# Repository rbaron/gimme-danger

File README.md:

An open source [USB Power Delivery](https://en.wikipedia.org/wiki/USB_hardware#USB_Power_Delivery) trigger board and 5-channel PWM controller that runs [ESPHome](https://esphome.io).

_GIMME DANGER!!_ negotiates up to 21 V and 3 A[^1] from a USB Power Delivery (USB-PD) capable source -- such as common USB-C wall adapters/chargers and power banks -- and provides controls for its 5 PWM channels, optionally via [Home Assistant](https://home-assistant.io). Each channel can be used to interface with LEDs, motors and more. See below for some video demos.

# Hardware

* [ESP32-S3](https://www.espressif.com/en/products/socs/esp32-s3) module, mounted on the [back of the PCB](./media/gimme-danger-back.jpg)
* [FUSB302B](https://www.onsemi.com/products/interfaces/usb-type-c/fusb302b) USB-PD controller
* [INA219](https://www.ti.com/product/INA219) current sensor
* 5 output PWM channels
* 2x5.5mm barrel jack for raw output voltage access
* Optional OLED display

The [`kicad/`](./kicad/) directory contains design files and fabrication files for [JLCPCB](https://jlcpcb.com) manufacturing and assembly. The big through-hole components (headers, power terminals) and the ESP32-S3 module are not included in the assembly, and expected to be soldered by hand.

# Software
A custom `fusb302` component was implemented in ESPHome to support this project. It currently lives in its own fork on [github.com/rbaron/tree/fusb302](https://github.com/rbaron/esphome/tree/fusb302).

Here's a minimal example of using our custom `fusb302` component with ESPHome:

```yaml
external_components:
  - source:
      type: git
      url: https://github.com/rbaron/esphome
      ref: fusb302
    components: [fusb302]

fusb302:
  id: fusb302_id
  i2c_id: i2c_bus_fusb302
  interrupt_pin: GPIO5
  voltage: 12000 mV
  current: 1000 mA
  on_pd_negotiation_success:
    then:
      - switch.turn_on: load_switch
```

Full ESPHome configs for the demos below and more are available in the [`code/`](./code) directory.

# ‼️ Safety disclaimer ‼️
Configuration mistakes or software bugs may toast your devices if a high voltage is accidentally negotiated. While I have never run into these issues, even during development, be extra mindful of this fact then using this project or the `fusb302` component separately. For all intents and purposes, this is an experimental project. Use it at your own risk.

# Supported Power Delivery features
* USB-PD 2.0 Fixed voltages -- 5V, 9V, 12V, 15V, 20V
* USB-PD 3.0 Programmable Power Supply (PPS) -- 3.3V-21V, in 20mV steps (see the power supply demo below)
* USB-PD 3.1 Extended Power Range (EPR) Fixed PDOs -- 28V[^1]

Support for USB-PD 3.1 Adjustable Voltage Supply (AVS) in EPR mode will let us pull 15-28V[^1]. Unfortunately it's still difficult to get our hands on EPR AVS capable sources to implement and test support for it, but in theory the heavy lifting is already done.

# Some use cases & demos
Below there are some demo videos. Click on the images to play.

## 12V LED strip
The main motivation for this project was to power short runs of LED strips from USB-C chargers and control them via Home Assistant. Observing the maximum current and voltage[^1], it should be doable to light up a shelf, table, TV stand or any DYI project that requires only a couple of meters of 12V LED strips. Here [wled-calculator.github.io](https://wled-calculator.github.io/) should help with planning.

In the video below we see _GIMME DANGER!!_ connected to [Home Assistant](https://www.home-assistant.io), controlling a short 12V LED strip.

## 12V RGBW LED strip

## A lil' programmable power supply
What's fun is that we can negotiate voltages on the fly from USB-PD 3.0 sources that offer Programmable Power Supply (PPS) modes. Here we have a potentiometer that sets the target voltage, and a button that triggers the USB-PD negotiation for that voltage.

A tiny, experimental and largely untested power supply that's powered by the same USB-C charger as my [soldering iron](https://pine64.com/product/pinecil-smart-mini-portable-soldering-iron/)? Straight into my toolbox.

## A Home Assistant controlled power supply
As a display of the flexibility of ESPHome and Home Assistant, we can use _GIMME DANGER!!_ to make a WiFi-controlled power supply. This is an objectively terrible idea, but it's not _GIMME SAFETY!!_ after all. Disregarding the risk of accidentally toasting our loads either via a misclick or a bug, this may be useful for automating the collection of I-V curves.

# Optional OLED display
There are female pin headers on the board to connect an 0.91" OLED display like [this one from Aliexpress](https://aliexpress.com/item/1005004816561244.html). It's used to display the running voltage and current. There's also a cute animation when negotiation is succesful -- you can see it in the demos above.

# 3D printed case

The [`case/`](./case) directory contains a little 3D printable case. The PCB is optionally held in place by three M2 screws and threaded inserts.

# License
The hardware and associated design files are released under the [Creative Commons CC BY-SA 4.0](https://creativecommons.org/licenses/by-sa/4.0/) license. The code is released under the [MIT license](https://opensource.org/licenses/MIT).

# Attributions
The logo uses the [Faster One](https://fonts.google.com/specimen/Faster+One/about) font, released under the [Open Font License](https://openfontlicense.org/).

[^1]: FUSB302B's typical maximum voltage is 21 V, with 28 V as the absolute maximum. Each PWM channel is rated for 3 A. In theory the board supports up to 5 A, but a safer, better tested range is 21 V / 3 A in total.

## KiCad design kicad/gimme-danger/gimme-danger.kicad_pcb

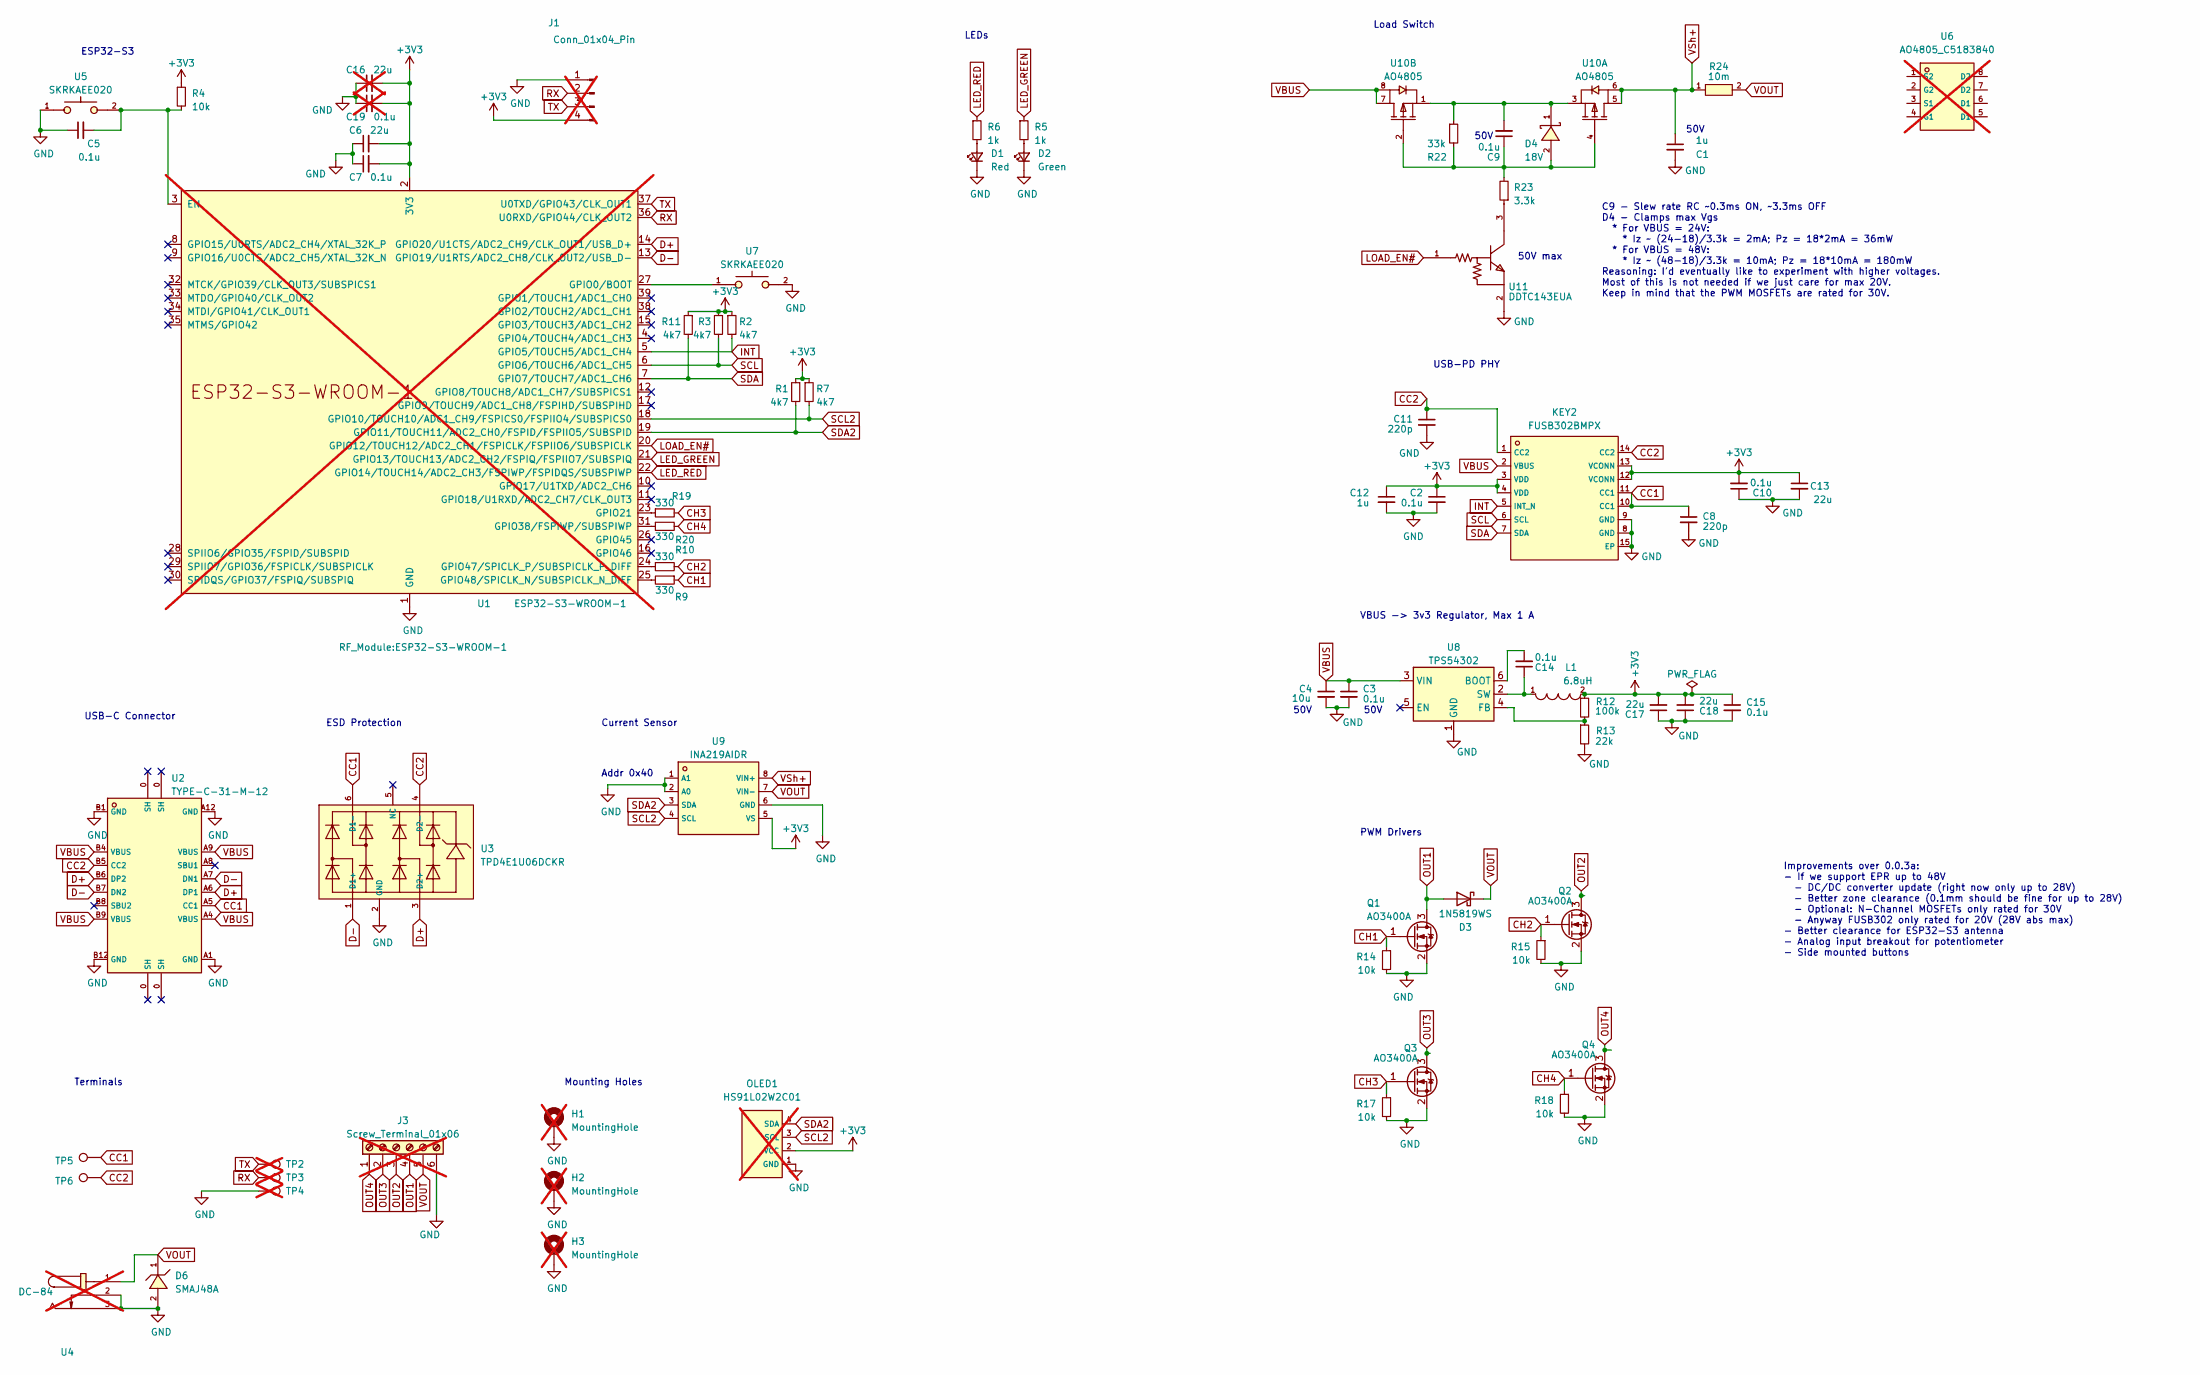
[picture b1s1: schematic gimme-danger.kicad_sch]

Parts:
C1: 1u; C_0603_1608Metric; LCSC C15849
C2, C3, C9, C10, C14, C15: 0.1u; C_0402_1005Metric; LCSC C307331
C4: 10u; C_0805_2012Metric; LCSC C440198
C5, C7: 0.1u; C_0402_1005Metric; LCSC C1525
C6, C13, C17, C18: 22u; C_0805_2012Metric; LCSC C45783
C8, C11: 220p; C_0402_1005Metric; LCSC C1530
C12: 1u; C_0402_1005Metric; LCSC C52923
C16: 22u; C_0805_2012Metric_Pad1.18x1.45mm_HandSolder; LCSC C45783; not fitted
C19: 0.1u; C_0805_2012Metric_Pad1.18x1.45mm_HandSolder; LCSC C1525; not fitted
D1: Red; LED_0805_2012Metric; LCSC C84256
D2: Green; LED_0805_2012Metric; LCSC C2297
D3: 1N5819WS; D_SOD-323
D4: 18V; SOD-523_L1.2-W0.8-LS1.6-RD; LCSC C327501
D6: SMAJ48A; SMA_L4.3-W2.5-LS5.0-RD; LCSC C353444
H1, H2, H3: MountingHole; MountingHole_2.2mm_M2_Pad_Via; not fitted
J1: Conn_01x04_Pin; PinHeader_1x04_P2.54mm_Vertical; not fitted
J3: Screw_Terminal_01x06; TerminalBlock_Phoenix_MKDS-1,5-6_1x06_P5.00mm_Horizontal; not fitted
KEY2: FUSB302BMPX; MLP-14_L2.5-W2.5-P0.50-BL-EP; LCSC C132291
L1: 6.8uH; IND-SMD_L4.5-W4.5_SMMS0420; LCSC C133194
OLED1: HS91L02W2C01; OLED-TH_L38.0-W12.0_HS91L02W2C01; LCSC C5248081; not fitted
Q1, Q2, Q3, Q4: AO3400A; SOT-23; LCSC C347475
R1, R2, R3, R7, R11: 4k7; R_0402_1005Metric; LCSC C25900
R4, R14, R15, R17, R18: 10k; R_0402_1005Metric; LCSC C25744
R5, R6: 1k; R_0402_1005Metric; LCSC C11702
R9, R10, R19, R20: 330; R_0402_1005Metric; LCSC C25104
R12: 100k; R_0402_1005Metric; LCSC C25741
R13: 22k; R_0402_1005Metric; LCSC C25768
R22: 33k; R_0402_1005Metric; LCSC C25779
R23: 3.3k; R_0402_1005Metric; LCSC C25890
R24: 10m; R2512; LCSC C105366
TP2, TP3, TP4: 3v3; TestPoint_Pad_D1.0mm; not fitted
TP5, TP6: 3v3; TestPoint_Pad_D1.0mm
U1: ESP32-S3-WROOM-1; not fitted
U2: TYPE-C-31-M-12; USB-C_SMD-TYPE-C-31-M-12; LCSC C165948
U3: TPD4E1U06DCKR; SC-70-6_L2.2-W1.3-P0.65-LS2.1-BL; LCSC C194628
U4: DC-84; DC-IN-TH_DC-84; LCSC C718040; not fitted
U5, U7: SKRKAEE020; SW-SMD_L3.9-W3.0-P4.45; LCSC C115357
U6: AO4805_C5183840; SOP-8_L4.9-W3.9-P1.27-LS6.0-BL; LCSC C5183840; not fitted
U8: TPS54302; SOT-23-6; LCSC C311983
U9: INA219AIDR; SOIC-8_L4.9-W3.9-P1.27-LS6.0-BL; LCSC C138706
U10: AO4805; SOIC-8_L4.9-W3.9-P1.27-LS6.0-BL; LCSC C5183840
U11: DDTC143EUA; SOT-323-3_L2.0-W1.3-P1.30-LS2.1-BR; LCSC C460045

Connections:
+3V3: C2.1, C6.2, C7.2, C10.2, C12.1, C13.1, C15.1, C16.2, C17.2, C18.2, C19.2, J1.4, KEY2.3 (VDD), KEY2.4 (VDD), KEY2.12 (VCONN), KEY2.13 (VCONN), L1.2, OLED1.2 (VCC), R1.1, R2.1, R3.1, R4.1, R7.1, R11.1, R12.1, U1.2 (3V3), U9.5 (VS)
CC1: C8.1, KEY2.10 (CC1), KEY2.11 (CC1), TP5.1, U2.A5 (CC1), U3.6 (D1-)
CC2: C11.1, KEY2.1 (CC2), KEY2.14 (CC2), TP6.1, U2.B5 (CC2), U3.4 (D2-)
CH1: Q1.1 (G), R9.1, R14.1
CH2: Q2.1 (G), R10.2, R15.1
CH3: Q3.1 (G), R17.1, R19.2
CH4: Q4.1 (G), R18.1, R20.2
D+: U1.14 (GPIO20/U1CTS/ADC2_CH9/CLK_OUT1/USB_D+), U2.A6 (DP1), U2.B6 (DP2), U3.3 (D2+)
D-: U1.13 (GPIO19/U1RTS/ADC2_CH8/CLK_OUT2/USB_D-), U2.A7 (DN1), U2.B7 (DN2), U3.1 (D1+)
GND: C1.2, C2.2, C3.2, C4.2, C5.1, C6.1, C7.1, C8.2, C10.1, C11.2, C12.2, C13.2, C15.2, C16.1, C17.1, C18.1, C19.1, D1.1 (K), D2.1 (K), D6.2 (A), H1.1, H2.1, H3.1, J1.1, J3.6, KEY2.8 (GND), KEY2.9 (GND), KEY2.15 (EP), OLED1.1 (GND), Q1.2 (S), Q2.2 (S), Q3.2 (S), Q4.2 (S), R13.2, R14.2, R15.2, R17.2, R18.2, TP4.1, U1.1 (GND), U1.40 (GND), U1.41 (GND), U2.A1 (GND), U2.A12 (GND), U2.B1 (GND), U2.B12 (GND), U3.2 (GND), U4.2, U4.3, U5.1, U7.2, U8.1 (GND), U9.1 (A1), U9.2 (A0), U9.6 (GND), U11.2 (GND(0))
INT: KEY2.5 (INT_N), R2.2, U1.5 (GPIO5/TOUCH5/ADC1_CH4)
LED_GREEN: R5.1, U1.21 (GPIO13/TOUCH13/ADC2_CH2/FSPIQ/FSPIIO7/S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)
LED_RED: R6.1, U1.22 (GPIO14/TOUCH14/ADC2_CH3/FSPIWP/FSPIDQS/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)
LOAD_EN#: U1.20 (GPIO12/TOUCH12/ADC2_CH1/FSPICLK/FSPIIO6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), U11.1 (IN)
unnamed: D1.2 (A), R6.2
unnamed: D2.2 (A), R5.2
unnamed: C9.1, D4.2 (A), R22.2, R23.2, U10.2 (G2), U10.4 (G1)
unnamed: C9.2, D4.1 (K), R22.1, U10.1 (S2), U10.3 (S1)
unnamed: C5.2, R4.2, U1.3 (EN), U5.2
unnamed: U1.27 (GPIO0/BOOT), U7.1
unnamed: R19.1, U1.23 (GPIO21)
unnamed: R20.1, U1.31 (GPIO38/FSPIWP/SUBSPIWP)
unnamed: R10.1, U1.24 (GPIO47/SPICLK_P/SUBSPICLK_P_DIFF)
unnamed: R9.2, U1.25 (GPIO48/SPICLK_N/SUBSPICLK_N_DIFF)
unnamed: C14.2, U8.6 (BOOT)
unnamed: R12.2, R13.1, U8.4 (FB)
unnamed: C14.1, L1.1, U8.2 (SW)
unnamed: R23.1, U11.3 (OUT)
OUT1: D3.2 (A), J3.4, Q1.3 (D)
OUT2: J3.3, Q2.3 (D)
OUT3: J3.2, Q3.3 (D)
OUT4: J3.1, Q4.3 (D)
RX: J1.2, TP3.1, U1.36 (U0RXD/GPIO44/CLK_OUT2)
SCL: KEY2.6 (SCL), R3.2, U1.6 (GPIO6/TOUCH6/ADC1_CH5)
SCL2: OLED1.3 (SCL), R7.2, U1.18 (GPIO10/TOUCH10/ADC1_CH9/FSPICS0/FSPIIO4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), U9.4 (SCL)
SDA: KEY2.7 (SDA), R11.2, U1.7 (GPIO7/TOUCH7/ADC1_CH6)
SDA2: OLED1.4 (SDA), R1.2, U1.19 (GPIO11/TOUCH11/ADC2_CH0/FSPID/FSPIIO5/S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), U9.3 (SDA)
TX: J1.3, TP2.1, U1.37 (U0TXD/GPIO43/CLK_OUT1)
VBUS: C3.1, C4.1, KEY2.2 (VBUS), U2.A4 (VBUS), U2.A9 (VBUS), U2.B4 (VBUS), U2.B9 (VBUS), U8.3 (VIN), U10.7 (D2), U10.8 (D2)
VOUT: D3.1 (K), D6.1 (C), J3.5, R24.2, U4.1, U9.7 (VIN-)
VSh+: C1.1, R24.1, U9.8 (VIN+), U10.5 (D1), U10.6 (D1)

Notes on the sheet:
ESD Protection
Mounting Holes
Terminals
50V
Current Sensor
50V max
Improvements over 0.0.3a: - If we support EPR up to 48V - DC/DC converter update (right now only up to 28V) - Better zone clearance (0.1mm should be fine for up to 28V) - Optional: N-Channel MOSFETs only rated for 30V - Anyway FUSB302 only rated for 20V (28V abs max) - Better clearance for ESP32-S3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
USB-C Connector
VBUS -> 3v3 Regulator, Max 1 A
PWM Drivers
LEDs
Load Switch
ESP32-S3
C9 - Slew rate RC ~0.3ms ON, ~3.3ms OFF D4 - Clamps max Vgs * For VBUS = 24V: * Iz ~ (24-18)/3.3k = 2mA; Pz = 18*2mA = 36mW * For VBUS = 48V: * Iz ~ (48-18)/3.3k = 10mA; Pz = 18*10mA = 180mW Reasoning: I'd eventually like to experiment with higher voltages. Most of this is not needed if we just car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
USB-PD PHY
Addr 0x40

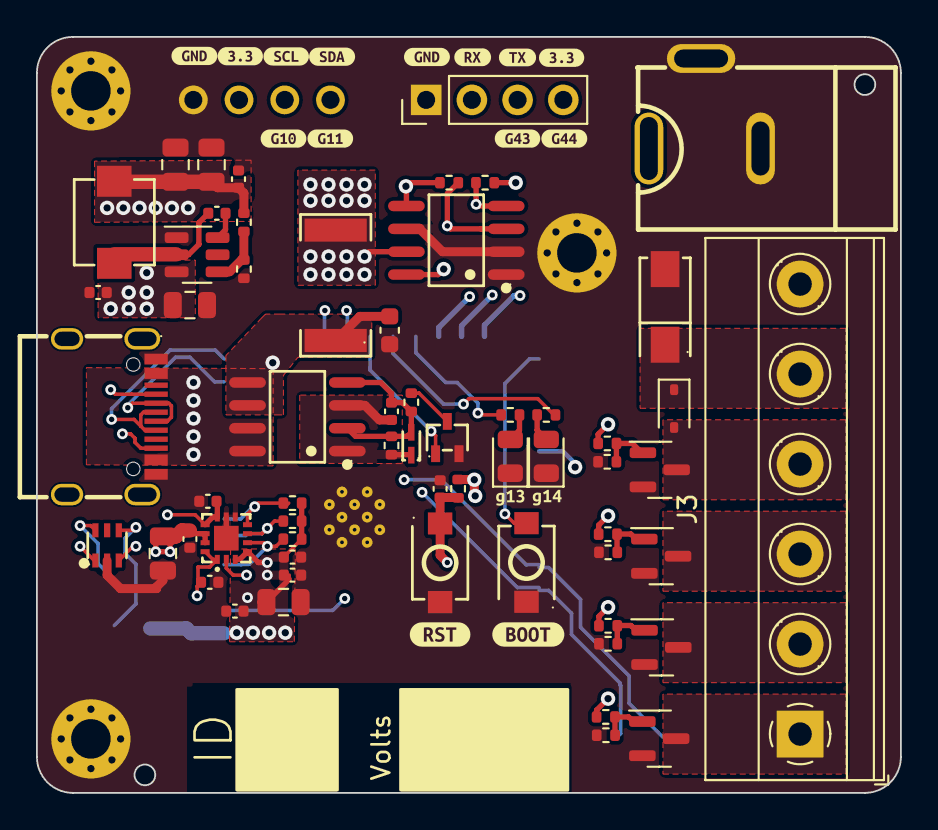
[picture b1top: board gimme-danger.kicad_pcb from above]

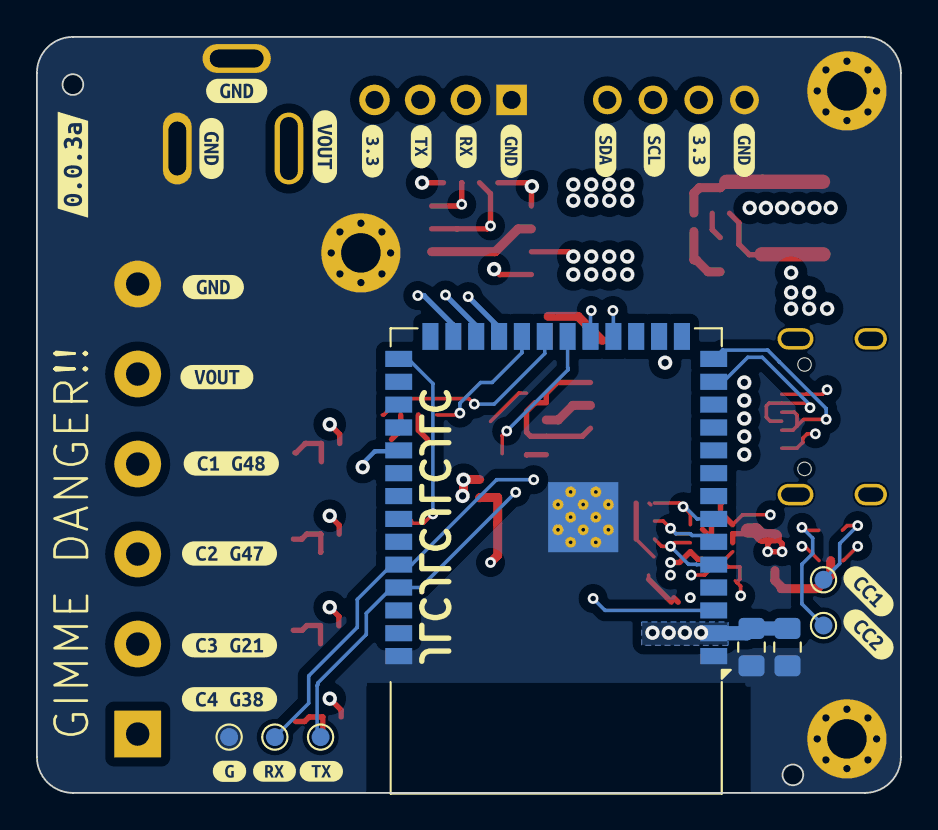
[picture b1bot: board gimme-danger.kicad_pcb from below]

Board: 4 copper layers, 48.0 x 42.0 mm, 112 parts (32 on the bottom side), 41 nets.

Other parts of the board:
kibuzzard-65EB08A1: G***; kibuzzard-65EB08A1
kibuzzard-65EB08B9: G***; kibuzzard-65EB08B9
kibuzzard-661F8A05, kibuzzard-661F8A05#2: G***; kibuzzard-661F8A05
kibuzzard-661F8A15: G***; kibuzzard-661F8A15
kibuzzard-661F8A20: G***; kibuzzard-661F8A20
kibuzzard-661F8A28: G***; kibuzzard-661F8A28
kibuzzard-661F9CA6: G***; kibuzzard-661F9CA6
kibuzzard-661F9CAC: G***; kibuzzard-661F9CAC
kibuzzard-661F9CB9: G***; kibuzzard-661F9CB9
kibuzzard-661F99AB: G***; kibuzzard-661F99AB
kibuzzard-661F999D: G***; kibuzzard-661F999D
kibuzzard-661F8503: G***; kibuzzard-661F8503
kibuzzard-661F8518: G***; kibuzzard-661F8518
kibuzzard-661F8521: G***; kibuzzard-661F8521
kibuzzard-661F9984: G***; kibuzzard-661F9984
kibuzzard-660044B0, kibuzzard-660044B0#2: G***; kibuzzard-660044B0
kibuzzard-660044E2: G***; kibuzzard-660044E2
kibuzzard-660044E7: G***; kibuzzard-660044E7
kibuzzard-660044F8: G***; kibuzzard-660044F8
kibuzzard-660044FF: G***; kibuzzard-660044FF
kibuzzard-660051B9: G***; kibuzzard-660051B9
kibuzzard-660051C1: G***; kibuzzard-660051C1
kibuzzard-660051C8: G***; kibuzzard-660051C8
kibuzzard-662001DF: G***; kibuzzard-662001DF
kibuzzard-662003AB: G***; kibuzzard-662003AB
kibuzzard-662003BE: G***; kibuzzard-662003BE
kibuzzard-662003E0: G***; kibuzzard-662003E0
kibuzzard-662003F5: G***; kibuzzard-662003F5
kibuzzard-662017BE: G***; kibuzzard-662017BE
kibuzzard-6600450E: G***; kibuzzard-6600450E
kibuzzard-6600453E: G***; kibuzzard-6600453E
kibuzzard-6600454F: G***; kibuzzard-6600454F
kibuzzard-6600455C: G***; kibuzzard-6600455C
kibuzzard-66004518: G***; kibuzzard-66004518
kibuzzard-66004529: G***; kibuzzard-66004529
kibuzzard-66004537: G***; kibuzzard-66004537
kibuzzard-66004547: G***; kibuzzard-66004547
kibuzzard-66004555: G***; kibuzzard-66004555

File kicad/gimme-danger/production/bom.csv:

Designator,Footprint,Quantity,Value,LCSC Part #
C1,0603,1,1u,C15849
"C10, C14, C15, C2, C3, C9",0402,6,0.1u,C307331
"C11, C8",0402,2,220p,C1530
C12,0402,1,1u,C52923
"C13, C17, C18, C6",0805,4,22u,C45783
C4,0805,1,10u,C440198
"C5, C7",0402,2,0.1u,C1525
D1,0805,1,Red,C84256
D2,0805,1,Green,C2297
D3,D_SOD-323,1,1N5819WS,
D4,SOD-523_L1.2-W0.8-LS1.6-RD,1,18V,C327501
D6,SMA_L4.3-W2.5-LS5.0-RD,1,SMAJ48A,C353444
KEY2,MLP-14_L2.5-W2.5-P0.50-BL-EP,1,FUSB302BMPX,C132291
L1,IND-SMD_L4.5-W4.5_SMMS0420,1,6.8uH,C133194
"Q1, Q2, Q3, Q4",SOT-23,4,AO3400A,C347475
"R1, R11, R2, R3, R7",0402,5,4k7,C25900
"R10, R19, R20, R9",0402,4,330,C25104
R12,0402,1,100k,C25741
R13,0402,1,22k,C25768
"R14, R15, R17, R18, R4",0402,5,10k,C25744
R22,0402,1,33k,C25779
R23,0402,1,3.3k,C25890
R24,R2512,1,10m,C105366
"R5, R6",0402,2,1k,C11702
U10,SOIC-8_L4.9-W3.9-P1.27-LS6.0-BL,1,AO4805,C5183840
U11,SOT-323-3_L2.0-W1.3-P1.30-LS2.1-BR,1,DDTC143EUA,C460045
U2,USB-C_SMD-TYPE-C-31-M-12,1,TYPE-C-31-M-12,C165948
U3,SC-70-6_L2.2-W1.3-P0.65-LS2.1-BL,1,TPD4E1U06DCKR,C194628
"U5, U7",SW-SMD_L3.9-W3.0-P4.45,2,SKRKAEE020,C115357
U8,SOT-23-6,1,TPS54302,C311983
U9,SOIC-8_L4.9-W3.9-P1.27-LS6.0-BL,1,INA219AIDR,C138706

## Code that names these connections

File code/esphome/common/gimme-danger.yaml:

esphome:
  name: gimmedanger003a${gimme_danger_device_id}
  friendly_name: Gimme Danger!! 0.0.3a ${gimme_danger_device_id}
  on_boot:
    - logger.log:
        format: "Gimme Danger!! 0.0.3a ${gimme_danger_device_id}"
        level: WARN
    - delay: 500ms
    - logger.log:
        format: "Starting PD negotiation"
        level: WARN
    - fusb302.start_power_negotiation:
        id: fusb302_id

esp32:
  board: esp32-s3-devkitc-1
  flash_size: 4MB

external_components:
  - source:
      type: git
      url: https://github.com/rbaron/esphome
      ref: fusb302
    components: [fusb302]

i2c:
  - id: i2c_bus_fusb302
    sda: GPIO7
    scl: GPIO6
    scan: False
    frequency: 100kHz
  - id: i2c_bus_ina
    sda: GPIO11
    scl: GPIO10
    scan: False
    frequency: 400kHz

logger:
  hardware_uart: UART0
  level: INFO

output:
  - platform: gpio
    pin:
      number: 13
      mode: output
    id: yellow_led
  - platform: gpio
    pin:
      number: 14
      mode: output
    id: red_led
  - platform: ledc
    id: output_ch1
    pin: GPIO48
  - platform: ledc
    id: output_ch2
    pin: GPIO47
  - platform: ledc
    id: output_ch3
    pin: GPIO21
  - platform: ledc
    id: output_ch4
    pin: GPIO38

switch:
  - platform: gpio
    pin: GPIO12
    id: load_switch
    name: Load Switch
    icon: mdi:flash

sensor:
  - id: ina219_sensor
    platform: ina219
    i2c_id: i2c_bus_ina
    address: 0x40
    shunt_resistance: 0.01 ohm
    current:
      id: ina219_current
      name: "Current"
    power:
      name: "Power"
    bus_voltage:
      id: ina219_load_voltage
      name: "Load Voltage"
    shunt_voltage:
      name: "Shunt Voltage"
    max_voltage: 28.0V
    max_current: 5A
    update_interval: 500ms

fusb302:
  id: fusb302_id
  i2c_id: i2c_bus_fusb302
  interrupt_pin: GPIO5
  voltage: 5000 mV
  current: 1000 mA
  start_power_negotiation_on_boot: false
  on_pd_negotiation_success:
    then:
      - output.turn_on: yellow_led
      - output.turn_off: red_led
      - switch.turn_on: load_switch
  on_pd_negotiation_failure:
    then:
      - output.turn_off: yellow_led
      - output.turn_on: red_led
      - switch.turn_off: load_switch
      - lambda: |-
          ESP_LOGW("fusb302_trigger", "PD negotiation failure outcome: %d", success);

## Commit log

2023-11-22 Forked sample, added nucleo_g071rb.overlay
    Miraculously it compiles? Still I need to wait for the nucleo_g071rb
    board. It should arrive tomorrow.
2023-11-25 Experiment in baremetal blinky
2023-11-25 Shuffle files around
2024-01-15 Initial kicad project -- just main ICs
2024-01-15 Set up page details
2024-01-19 Add NX20P5090 IC for switching
2024-01-20 First pass on schematics -- needs double checking, esp decoupling caps
2024-01-21 Second pass on schematics
2024-01-21 Changed to more capable DC-DC converter (up to 1.2A)
    Worst case: ESP32-S3 500 mA + FUSB302 500 mA
2024-01-24 Initial partial routing
    But I'm not convinced I can route the tiny load switch well. I will
    change it back to the same setup as used by luz.
2024-03-06 Schematic with FUSB302 kinda finished
2024-03-06 Better schematic layout
2024-03-07 Initial partial routing
2024-03-07 Initial routing
    Many issues :|
2024-03-07 DRC kinda passes
2024-03-08 Minor routing fixes
2024-03-08 Routed new output: 4 channels
2024-03-08 Better ground return path for all channels
2024-03-08 Removed some unconnected tracks
2024-03-08 v0.0.1a maybe?
2024-03-08 No mo 0.2 vias -> 0.3 vias
2024-03-08 Fixes DRC errors
2024-03-08 Moar VBus zone
2024-03-10 Production 0.0.1a
2024-03-15 Blinky kinda works! But boards needs revision...
2024-03-17 (Fixed) PD negotiation and V out monitor works :)
2024-03-17 Typo
2024-03-22 YAML for 4 channels + wifi + fusb302
2024-03-23 New load switch design
2024-03-24 Notes
2024-03-24 TVS diodes on output
2024-03-24 Added mounting holes
2024-03-24 v0.0.2a routing v0
2024-03-24 Board outline is round number of mms
2024-03-24 Add schottky on ch1
2024-03-24 No more DRC errors -- only 78 warnings
2024-03-24 Routing 0.0.2a v1
    No DCR errors
2024-03-25 Changed PWM drivers gate resistor to 330
    Minor routing changes
2024-03-25 v0.0.2a fabrication
2024-04-01 .gitignore
2024-04-01 Updated to KiCad 8
    Also updated ESP32-S3 footprint/model
2024-04-05 Add case
2024-04-13 Debug notes
2024-04-15 New debug files
2024-04-15 Kicad comments
2024-04-17 First routing of 0.0.3a
2024-04-17 DRC passes for 0.0.3a
2024-04-17 Final touches on 0.0.3a
2024-04-17 Minor tweaks
2024-04-17 Fabrication output for 0.0.3a
2024-04-26 Organizing dirs for 0.0.3a
2024-04-27 0.0.3a files work
2024-05-05 Don't ask
2024-05-05 Packaging wifi
2024-05-08 PSU + WiFi PSU yamls
2024-05-08 Big cleanup
2024-05-08 Organize esphome code
2024-05-08 esp-idf example
2024-05-08 Set default log level to WARN
2024-05-09 Cleanup & logic2 example captures
2024-05-09 It works on raspberry pi pico!
2024-05-09 It works on esp32-c6
2024-05-09 Cleanup old code
2024-05-09 Initial README.md
2024-05-09 Updated README and uses external_components
2024-05-09 Add external_component to examples for other platforms
2024-05-09 Typo in README.md
2024-05-09 More README.md editing
2024-05-09 Remove old .devcontainer
2024-05-09 Add font attribution
2026-05-24 Upgrade esphome version
